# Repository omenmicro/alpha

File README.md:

# OMEN Alpha - [[česky](README-CZ.md)]

_8bit computer, based on 8085 CPU._

- [Essential ICs on AliExpress](https://alitronik.com/omen-alpha-pack/)
- [Essential ICs on eBay](https://alitronik.com/omen-alpha-pack-ebay/)

[BOM - Needed parts](./BOM.md)

I write a book about old computers. Oh, sorry: I mean "vintage computers" from the 80's. My primary goal is to show how one can build an 8bit computer from scratch.

It means: how to set up a CPU, how to connect memories, how to connect peripheral chips, and why to connect...

This computer is a "demo construction": A computer, based on 8085 CPU, with 32 kB of (EEP)ROM and 32 kB of RAM, serial connection and parallel ports. All should be as simple as possible. And here is a result.

ROM
---

Use the last Monitor file - see [sw/Monitor/v4](sw/Monitor/v4)

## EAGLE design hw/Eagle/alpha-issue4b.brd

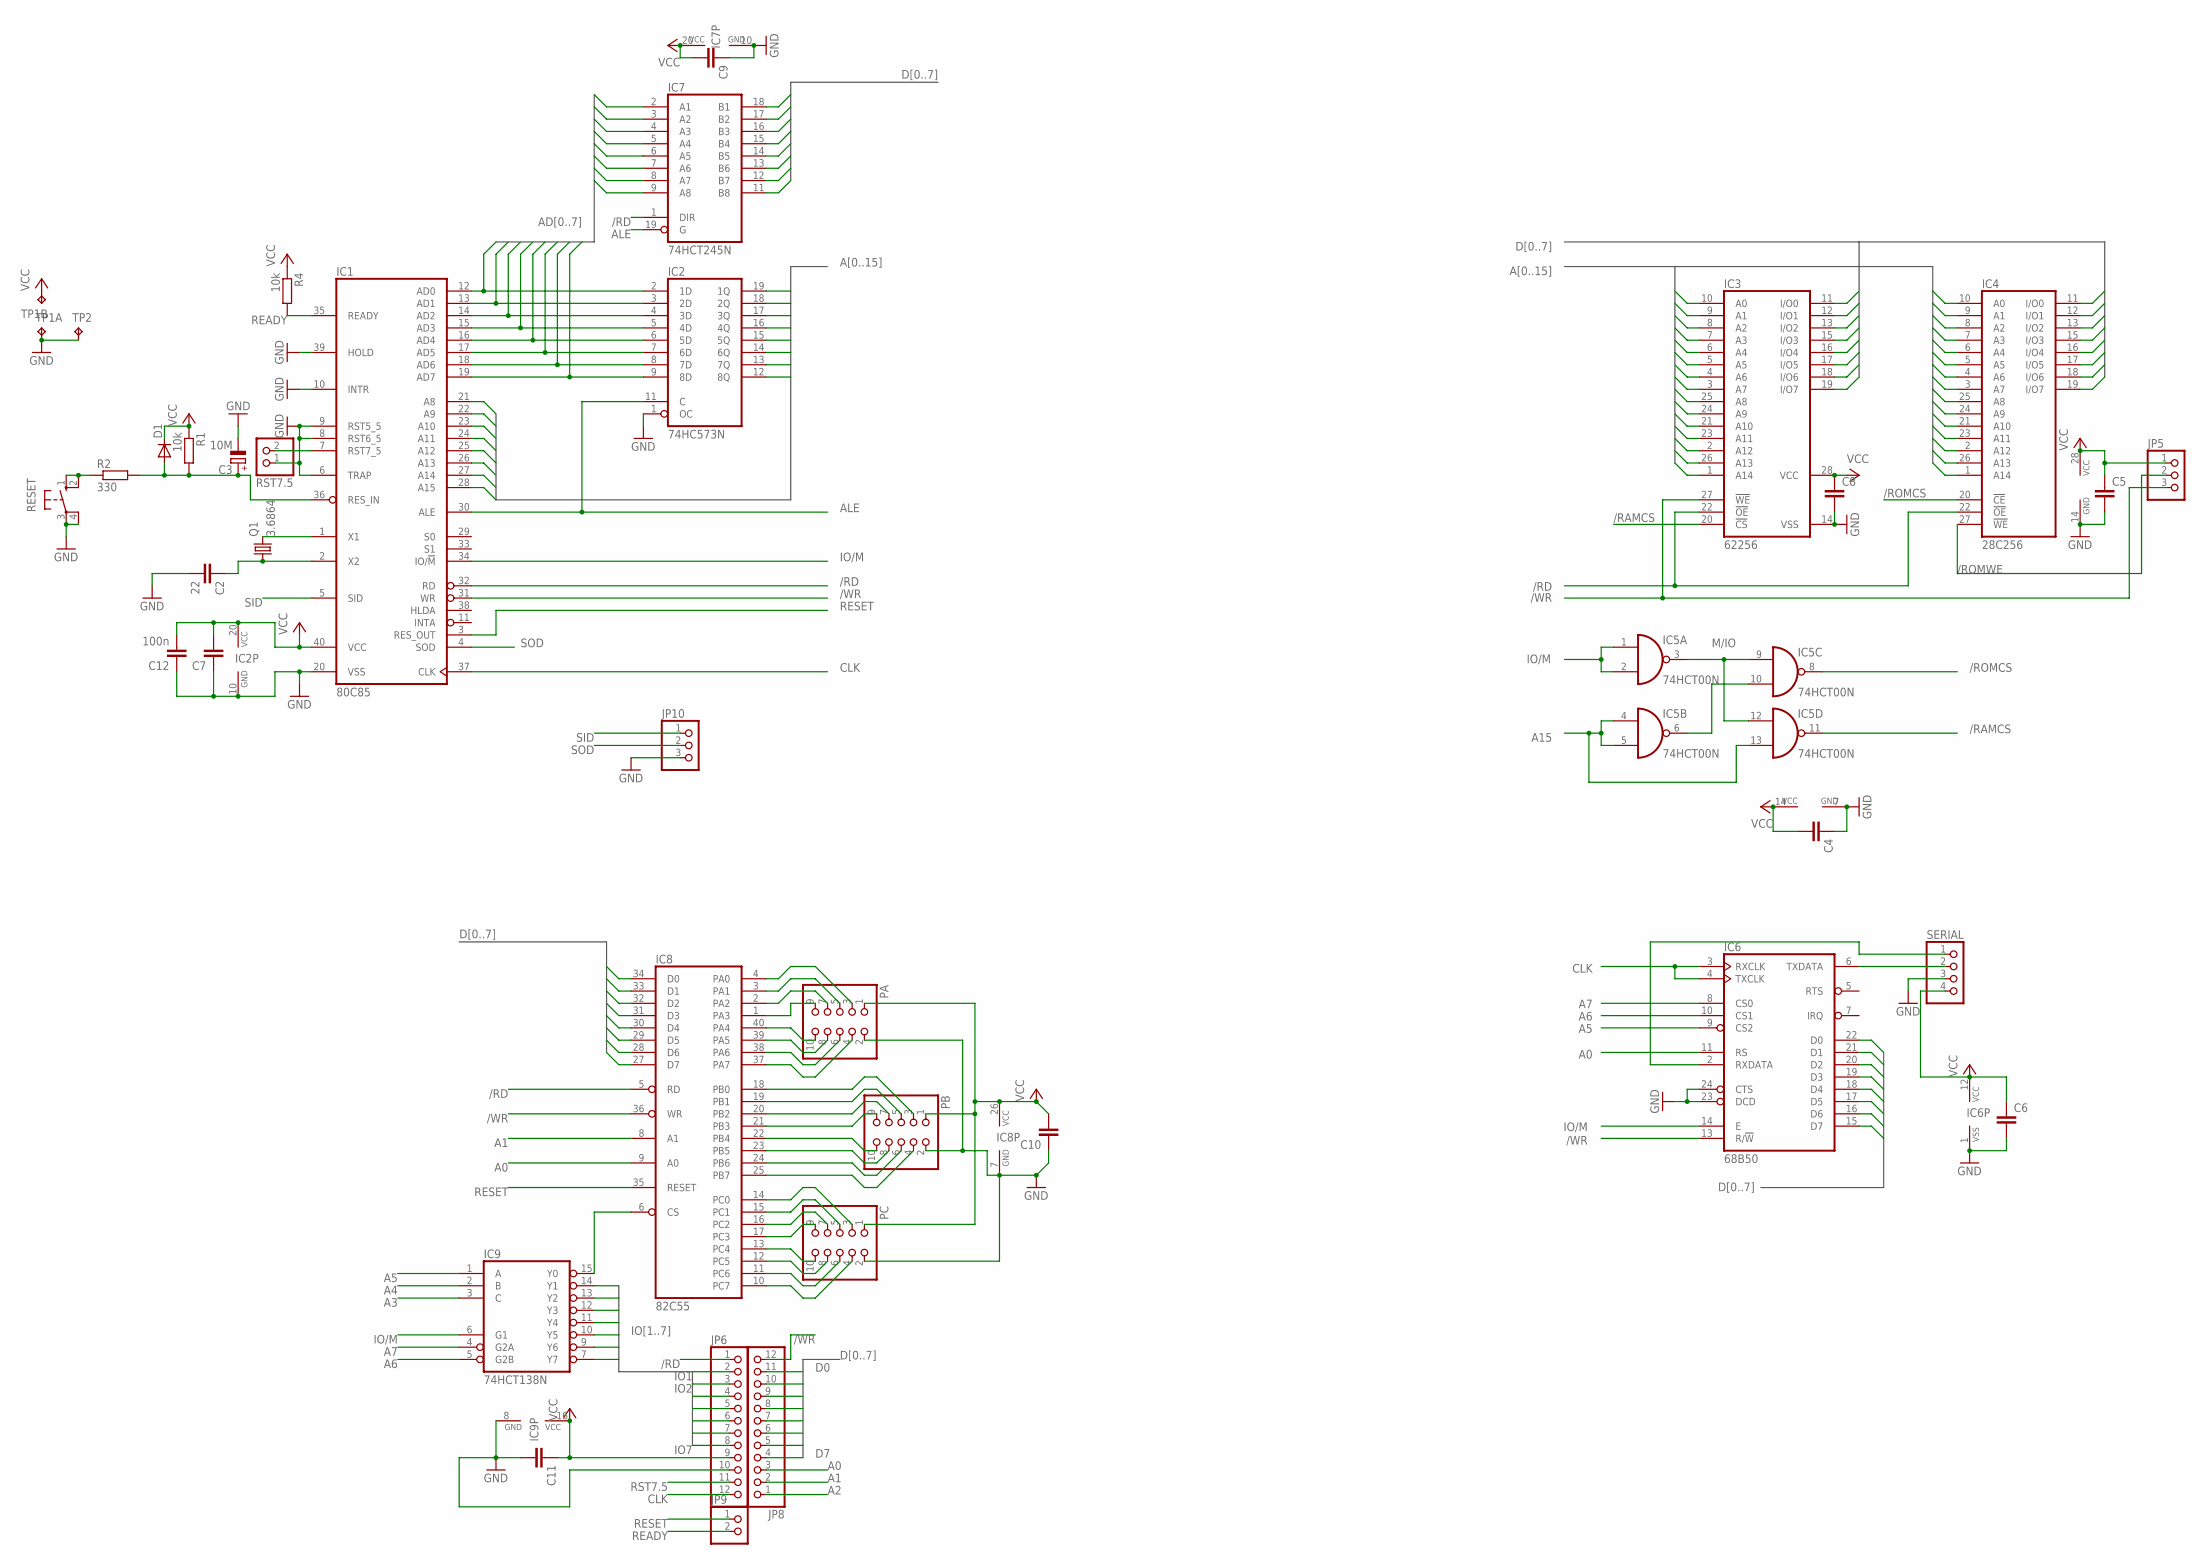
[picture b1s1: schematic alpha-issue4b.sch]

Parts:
C2: 22; C025-040X050
C3: 10M; E5-8,5
C4, C5, C6, C7, C8, C9, C10, C11: C-EU050-025X075; C050-025X075
C12: 100n; C050-025X075
D1: 1N4004; DO41-10
IC1: 80C85; DIL40
IC2: 74HC573N; DIL20
IC3: 62256; DIL28-6
IC4: 28C256; DIL28
IC5: 74HCT00N; DIL14
IC6: 68B50; DIL24
IC7: 74HCT245N; DIL20
IC8: 82C55; DIL40
IC9: 74HCT138N; DIL16
JP5, JP10: PINHD-1X3; 1X03
JP6, JP8: PINHD-1X12; 1X12
JP9: PINHD-1X2; 1X02
PA: PINHD-2X5; 2X05
PB: PINHD-2X5; 2X05
PC: PINHD-2X5; 2X05
Q1: 3.6864; HC49/S
R1: 10k; 0207/10
R2: 330; 0207/10
R4: 10k; 0204/7
RESET: 40-XX; B3F-40XX
RST7.5: PINHD-1X2; 1X02
SERIAL: PINHD-1X4; 1X04
TP1: TP2P2-38-17; P2-38-17
TP2: TPPAD1-17Y; P1-17Y

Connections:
/RAMCS: IC3.20 (!CS), IC5.11 (O)
/RD: IC1.32 (RD), IC3.22 (!OE), IC4.22 (!OE), IC7.1 (DIR), IC8.5 (RD), JP6.1
/ROMCS: IC4.20 (!CE), IC5.8 (O)
/ROMWE: IC4.27 (!WE), JP5.2
/WR: IC1.31 (WR), IC3.27 (!WE), IC6.13 (R/!W), IC8.36 (WR), JP5.3, JP8.12
A0: IC2.19 (1Q), IC3.10 (A0), IC4.10 (A0), IC6.11 (RS), IC8.9 (A0), JP8.3
A1: IC2.18 (2Q), IC3.9 (A1), IC4.9 (A1), IC8.8 (A1), JP8.2
A2: IC2.17 (3Q), IC3.8 (A2), IC4.8 (A2), JP8.1
A3: IC2.16 (4Q), IC3.7 (A3), IC4.7 (A3), IC9.3 (C)
A4: IC2.15 (5Q), IC3.6 (A4), IC4.6 (A4), IC9.2 (B)
A5: IC2.14 (6Q), IC3.5 (A5), IC4.5 (A5), IC6.9 (CS2), IC9.1 (A)
A6: IC2.13 (7Q), IC3.4 (A6), IC4.4 (A6), IC6.10 (CS1), IC9.5 (G2B)
A7: IC2.12 (8Q), IC3.3 (A7), IC4.3 (A7), IC6.8 (CS0), IC9.4 (G2A)
A8: IC1.21 (A8), IC3.25 (A8), IC4.25 (A8)
A9: IC1.22 (A9), IC3.24 (A9), IC4.24 (A9)
A10: IC1.23 (A10), IC3.21 (A10), IC4.21 (A10)
A11: IC1.24 (A11), IC3.23 (A11), IC4.23 (A11)
A12: IC1.25 (A12), IC3.2 (A12), IC4.2 (A12)
A13: IC1.26 (A13), IC3.26 (A13), IC4.26 (A13)
A14: IC1.27 (A14), IC3.1 (A14), IC4.1 (A14)
A15: IC1.28 (A15), IC5.4 (I0), IC5.5 (I1), IC5.13 (I1)
ALE: IC1.30 (ALE), IC2.11 (C), IC7.19 (G)
CLK: IC1.37 (CLK), IC6.3 (RXCLK), IC6.4 (TXCLK), JP6.12
D0: IC3.11 (I/O0), IC4.11 (I/O0), IC6.22 (D0), IC7.18 (B1), IC8.34 (D0), JP8.11
D1: IC3.12 (I/O1), IC4.12 (I/O1), IC6.21 (D1), IC7.17 (B2), IC8.33 (D1), JP8.10
D2: IC3.13 (I/O2), IC4.13 (I/O2), IC6.20 (D2), IC7.16 (B3), IC8.32 (D2), JP8.9
D3: IC3.15 (I/O3), IC4.15 (I/O3), IC6.19 (D3), IC7.15 (B4), IC8.31 (D3), JP8.8
D4: IC3.16 (I/O4), IC4.16 (I/O4), IC6.18 (D4), IC7.14 (B5), IC8.30 (D4), JP8.7
D5: IC3.17 (I/O5), IC4.17 (I/O5), IC6.17 (D5), IC7.13 (B6), IC8.29 (D5), JP8.6
D6: IC3.18 (I/O6), IC4.18 (I/O6), IC6.16 (D6), IC7.12 (B7), IC8.28 (D6), JP8.5
D7: IC3.19 (I/O7), IC4.19 (I/O7), IC6.15 (D7), IC7.11 (B8), IC8.27 (D7), JP8.4
DX0: IC1.12 (AD0), IC2.2 (1D), IC7.2 (A1)
DX1: IC1.13 (AD1), IC2.3 (2D), IC7.3 (A2)
DX2: IC1.14 (AD2), IC2.4 (3D), IC7.4 (A3)
DX3: IC1.15 (AD3), IC2.5 (4D), IC7.5 (A4)
DX4: IC1.16 (AD4), IC2.6 (5D), IC7.6 (A5)
DX5: IC1.17 (AD5), IC2.7 (6D), IC7.7 (A6)
DX6: IC1.18 (AD6), IC2.8 (7D), IC7.8 (A7)
DX7: IC1.19 (AD7), IC2.9 (8D), IC7.9 (A8)
GND: C2.2, C3.-, C4.1, C5.2, C6.2, C7.1, C8.2, C9.1, C10.1, C11.2, C12.1, IC1.6 (TRAP), IC1.8 (RST6_5), IC1.9 (RST5_5), IC1.10 (INTR), IC1.20 (VSS), IC1.39 (HOLD), IC2.1 (OC), IC2.10 (GND), IC3.14 (VSS), IC4.14 (GND), IC5.7 (GND), IC6.1 (VSS), IC6.23 (DCD), IC6.24 (CTS), IC7.10 (GND), IC8.7 (GND), IC9.8 (GND), JP6.10, JP10.3, PA.2, PB.2, PC.2, RESET.3, RESET.4 (P1), RST7.5.1, SERIAL.3, TP1.TP-1, TP2.TP
IO1: IC9.14 (Y1), JP6.2
IO2: IC9.13 (Y2), JP6.3
IO3: IC9.12 (Y3), JP6.4
IO4: IC9.11 (Y4), JP6.5
IO5: IC9.10 (Y5), JP6.6
IO6: IC9.9 (Y6), JP6.7
IO7: IC9.7 (Y7), JP6.8
IO/M: IC1.34 (IO/!M), IC5.1 (I0), IC5.2 (I1), IC6.14 (E), IC9.6 (G1)
M/IO: IC5.3 (O), IC5.9 (I0), IC5.12 (I0)
unnamed: IC1.1 (X1), Q1.2
unnamed: C2.1, IC1.2 (X2), Q1.1
unnamed: IC6.6 (TXDATA), SERIAL.2
unnamed: C3.+, D1.A, IC1.36 (RES_IN), R1.2, R2.2
unnamed: R2.1, RESET.1 (S), RESET.2 (S1)
unnamed: IC5.6 (O), IC5.10 (I1)
unnamed: IC8.1 (PA3), PA.9
unnamed: IC6.2 (RXDATA), SERIAL.1
unnamed: IC8.2 (PA2), PA.7
unnamed: IC8.3 (PA1), PA.5
unnamed: IC8.4 (PA0), PA.3
unnamed: IC8.40 (PA4), PA.10
unnamed: IC8.39 (PA5), PA.8
unnamed: IC8.38 (PA6), PA.6
unnamed: IC8.37 (PA7), PA.4
unnamed: IC8.21 (PB3), PB.9
unnamed: IC8.20 (PB2), PB.7
unnamed: IC8.19 (PB1), PB.5
unnamed: IC8.18 (PB0), PB.3
unnamed: IC8.22 (PB4), PB.10
unnamed: IC8.23 (PB5), PB.8
unnamed: IC8.24 (PB6), PB.6
unnamed: IC8.25 (PB7), PB.4
unnamed: IC8.17 (PC3), PC.9
unnamed: IC8.13 (PC4), PC.10
unnamed: IC8.16 (PC2), PC.7
unnamed: IC8.15 (PC1), PC.5
unnamed: IC8.12 (PC5), PC.8
unnamed: IC8.11 (PC6), PC.6
unnamed: IC8.6 (CS), IC9.15 (Y0)
PORTC0: IC8.14 (PC0), PC.3
PORTC7: IC8.10 (PC7), PC.4
READY: IC1.35 (READY), JP9.2, R4.2
RESET: IC1.3 (RES_OUT), IC8.35 (RESET), JP9.1
RST7.5: IC1.7 (RST7_5), JP6.11, RST7.5.2
SID: IC1.5 (SID), JP10.1
SOD: IC1.4 (SOD), JP10.2
VCC: C4.2, C5.1, C6.1, C7.2, C8.1, C9.2, C10.2, C11.1, C12.2, D1.C, IC1.40 (VCC), IC2.20 (VCC), IC3.28 (VCC), IC4.28 (VCC), IC5.14 (VCC), IC6.12 (VCC), IC7.20 (VCC), IC8.26 (VCC), IC9.16 (VCC), JP5.1, JP6.9, PA.1, PB.1, PC.1, R1.1, R4.1, SERIAL.4, TP1.TP-2

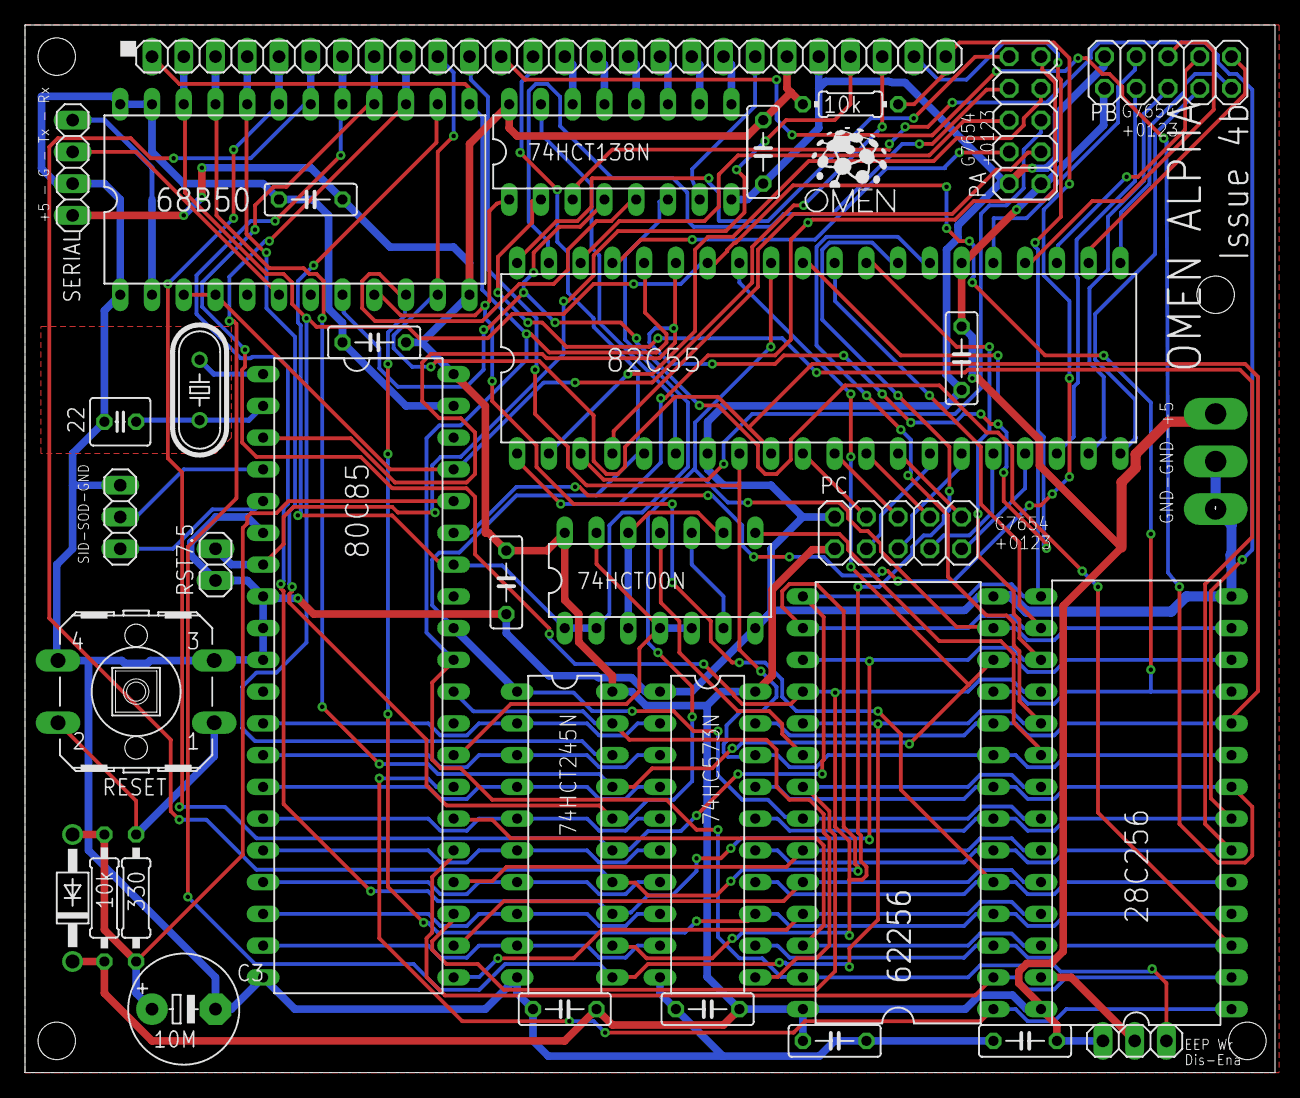
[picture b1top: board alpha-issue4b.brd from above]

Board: 2 copper layers, 100.0 x 83.8 mm, 38 parts (0 on the bottom side), 87 nets.

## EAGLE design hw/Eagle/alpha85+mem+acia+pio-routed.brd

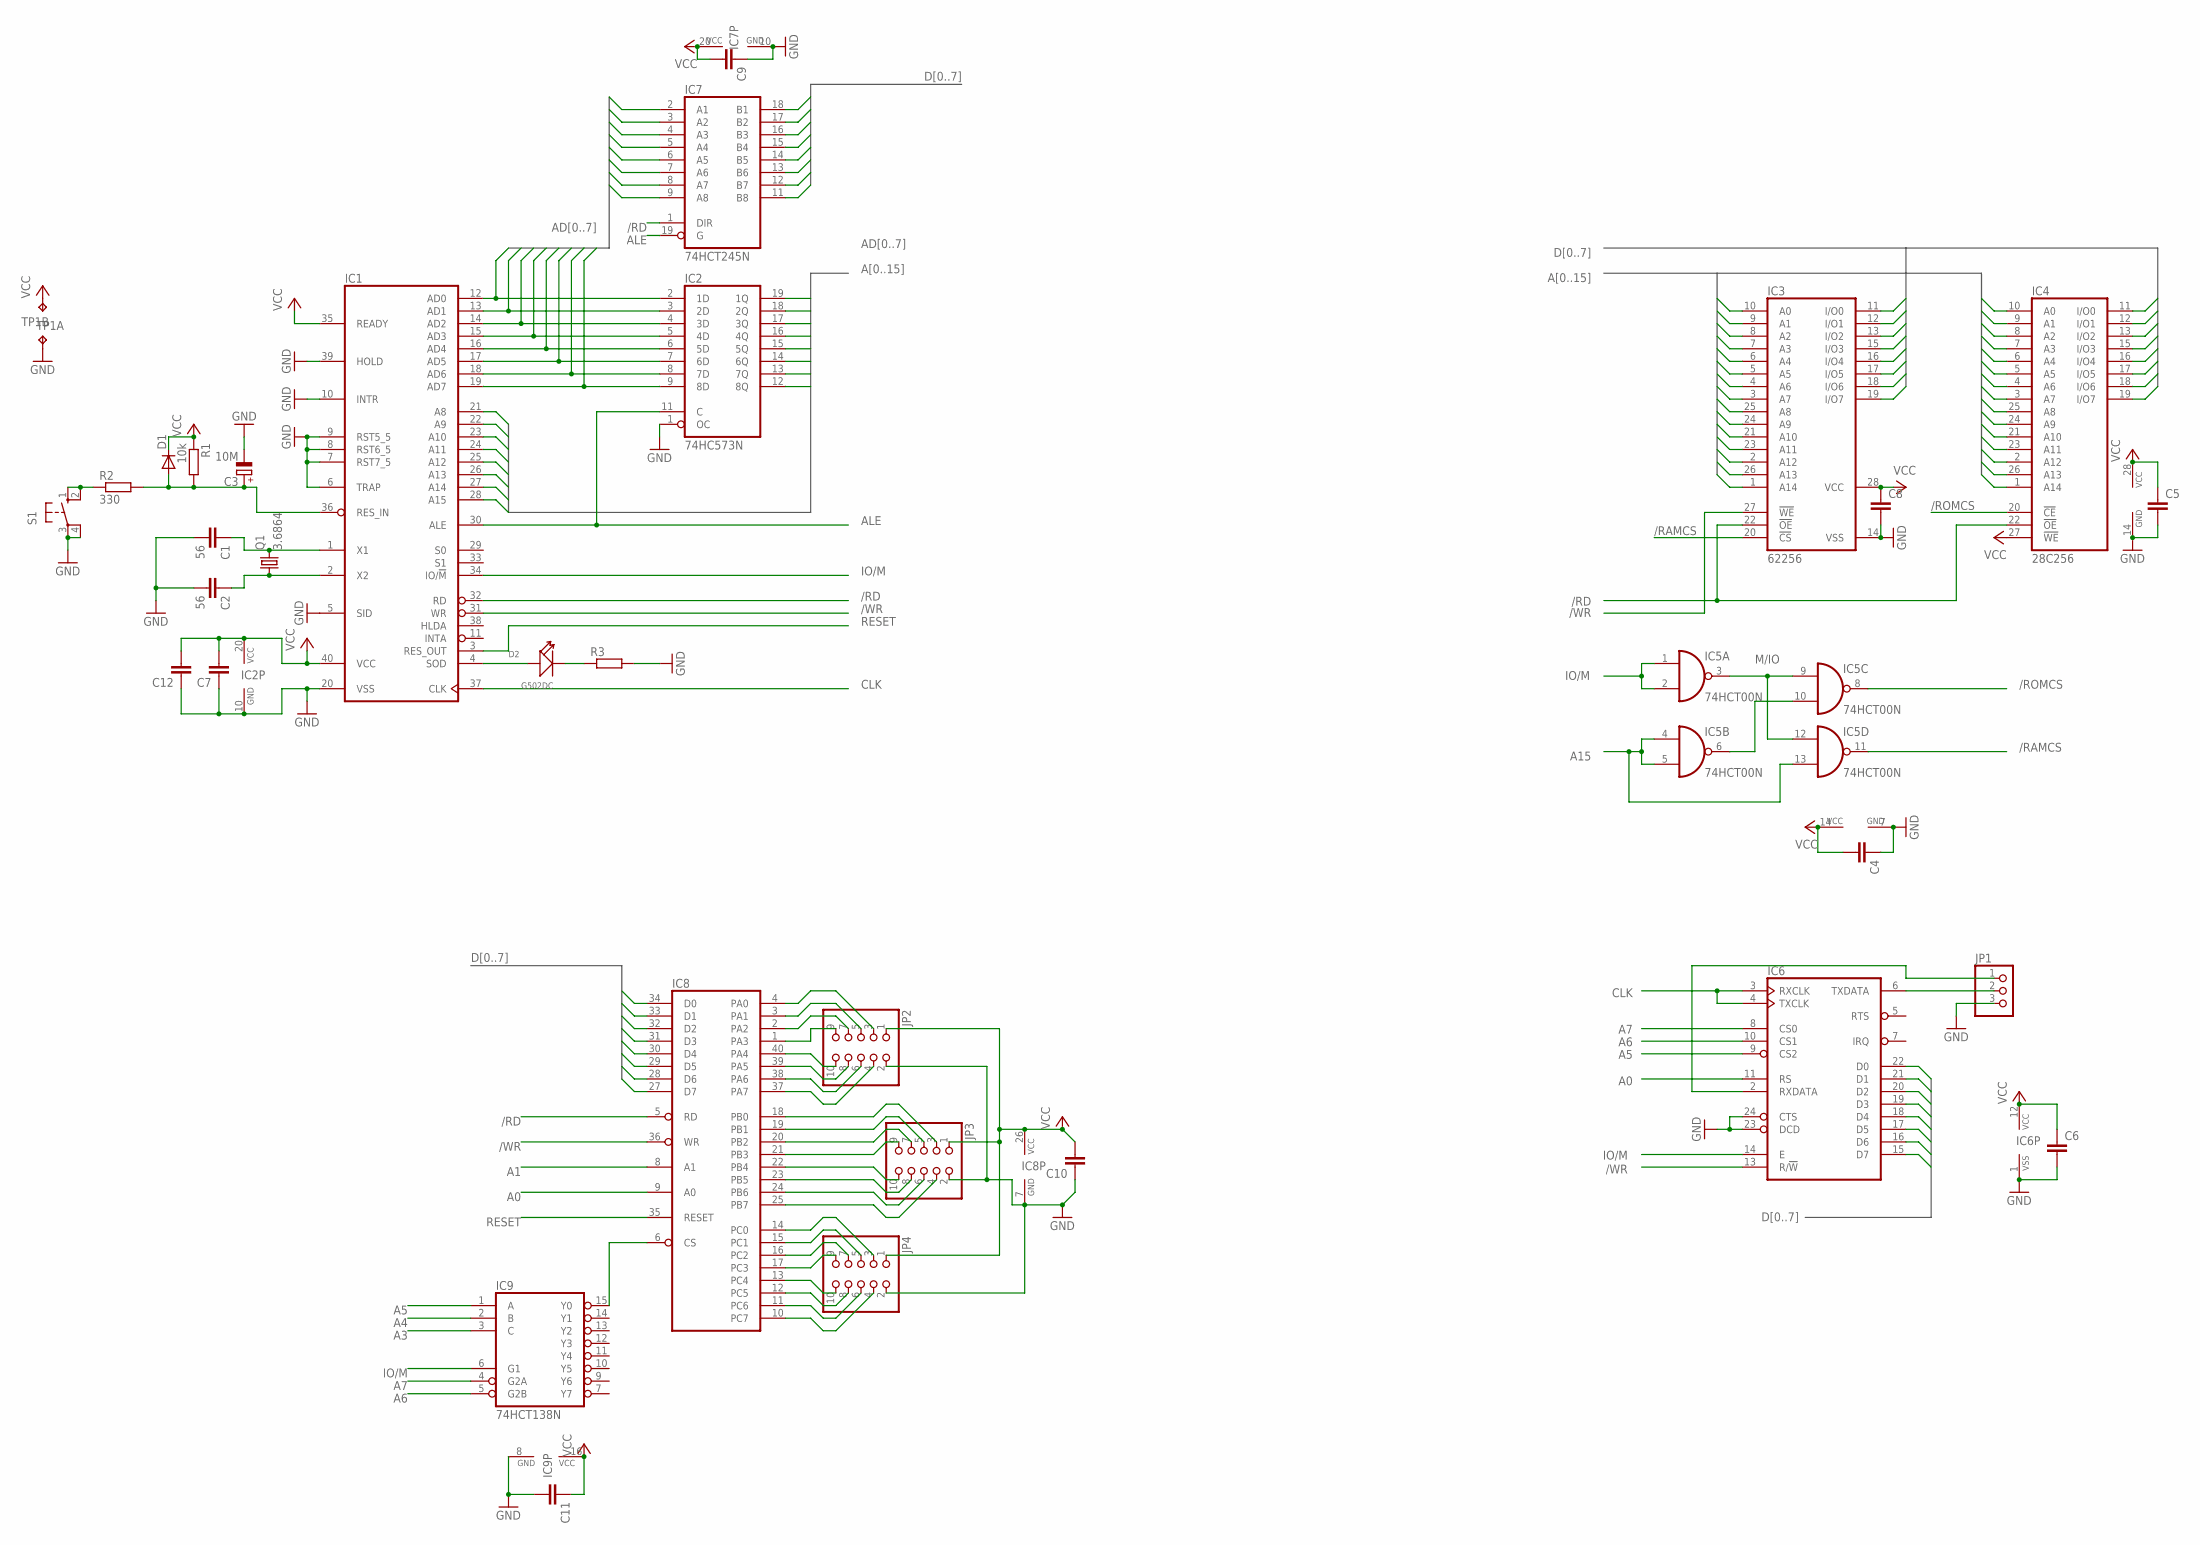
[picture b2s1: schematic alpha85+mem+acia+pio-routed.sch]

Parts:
C1, C2: 56; C025-040X050
C3: 10M; E5-8,5
C4, C5, C6, C7, C8, C9, C10, C11, C12: C-EU050-025X075; C050-025X075
D1: 1N4004; DO41-10
D2: G502DC; LED2-2.54-D5.0MM
IC1: 8085; DIL40
IC2: 74HC573N; DIL20
IC3: 62256; DIL28-6
IC4: 28C256; DIL28
IC5: 74HCT00N; DIL14
IC6: 6850; DIL24
IC7: 74HCT245N; DIL20
IC8: 8255A; DIL40
IC9: 74HCT138N; DIL16
JP1: PINHD-1X3; 1X03
JP2, JP3, JP4: PINHD-2X5; 2X05
Q1: 3.6864; HC49/S
R1: 10k; 0207/10
R2: 330; 0207/10
R3: R-EU_0207/7; 0207/7
S1: 40-XX; B3F-40XX
TP1: TP2P2-38-17; P2-38-17

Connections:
/RAMCS: IC3.20 (!CS), IC5.11 (O)
/RD: IC1.32 (RD), IC3.22 (!OE), IC4.22 (!OE), IC7.1 (DIR), IC8.5 (RD)
/ROMCS: IC4.20 (!CE), IC5.8 (O)
/WR: IC1.31 (WR), IC3.27 (!WE), IC6.13 (R/!W), IC8.36 (WR)
A0: IC2.19 (1Q), IC3.10 (A0), IC4.10 (A0), IC6.11 (RS), IC8.9 (A0)
A1: IC2.18 (2Q), IC3.9 (A1), IC4.9 (A1), IC8.8 (A1)
A2: IC2.17 (3Q), IC3.8 (A2), IC4.8 (A2)
A3: IC2.16 (4Q), IC3.7 (A3), IC4.7 (A3), IC9.3 (C)
A4: IC2.15 (5Q), IC3.6 (A4), IC4.6 (A4), IC9.2 (B)
A5: IC2.14 (6Q), IC3.5 (A5), IC4.5 (A5), IC6.9 (CS2), IC9.1 (A)
A6: IC2.13 (7Q), IC3.4 (A6), IC4.4 (A6), IC6.10 (CS1), IC9.5 (G2B)
A7: IC2.12 (8Q), IC3.3 (A7), IC4.3 (A7), IC6.8 (CS0), IC9.4 (G2A)
A8: IC1.21 (A8), IC3.25 (A8), IC4.25 (A8)
A9: IC1.22 (A9), IC3.24 (A9), IC4.24 (A9)
A10: IC1.23 (A10), IC3.21 (A10), IC4.21 (A10)
A11: IC1.24 (A11), IC3.23 (A11), IC4.23 (A11)
A12: IC1.25 (A12), IC3.2 (A12), IC4.2 (A12)
A13: IC1.26 (A13), IC3.26 (A13), IC4.26 (A13)
A14: IC1.27 (A14), IC3.1 (A14), IC4.1 (A14)
A15: IC1.28 (A15), IC5.4 (I0), IC5.5 (I1), IC5.13 (I1)
ALE: IC1.30 (ALE), IC2.11 (C), IC7.19 (G)
CLK: IC1.37 (CLK), IC6.3 (RXCLK), IC6.4 (TXCLK)
D0: IC3.11 (I/O0), IC4.11 (I/O0), IC6.22 (D0), IC7.18 (B1), IC8.34 (D0)
D1: IC3.12 (I/O1), IC4.12 (I/O1), IC6.21 (D1), IC7.17 (B2), IC8.33 (D1)
D2: IC3.13 (I/O2), IC4.13 (I/O2), IC6.20 (D2), IC7.16 (B3), IC8.32 (D2)
D3: IC3.15 (I/O3), IC4.15 (I/O3), IC6.19 (D3), IC7.15 (B4), IC8.31 (D3)
D4: IC3.16 (I/O4), IC4.16 (I/O4), IC6.18 (D4), IC7.14 (B5), IC8.30 (D4)
D5: IC3.17 (I/O5), IC4.17 (I/O5), IC6.17 (D5), IC7.13 (B6), IC8.29 (D5)
D6: IC3.18 (I/O6), IC4.18 (I/O6), IC6.16 (D6), IC7.12 (B7), IC8.28 (D6)
D7: IC3.19 (I/O7), IC4.19 (I/O7), IC6.15 (D7), IC7.11 (B8), IC8.27 (D7)
DX0: IC1.12 (AD0), IC2.2 (1D), IC7.2 (A1)
DX1: IC1.13 (AD1), IC2.3 (2D), IC7.3 (A2)
DX2: IC1.14 (AD2), IC2.4 (3D), IC7.4 (A3)
DX3: IC1.15 (AD3), IC2.5 (4D), IC7.5 (A4)
DX4: IC1.16 (AD4), IC2.6 (5D), IC7.6 (A5)
DX5: IC1.17 (AD5), IC2.7 (6D), IC7.7 (A6)
DX6: IC1.18 (AD6), IC2.8 (7D), IC7.8 (A7)
DX7: IC1.19 (AD7), IC2.9 (8D), IC7.9 (A8)
GND: C1.2, C2.2, C3.-, C4.1, C5.2, C6.2, C7.1, C8.2, C9.1, C10.1, C11.2, C12.1, IC1.5 (SID), IC1.6 (TRAP), IC1.7 (RST7_5), IC1.8 (RST6_5), IC1.9 (RST5_5), IC1.10 (INTR), IC1.20 (VSS), IC1.39 (HOLD), IC2.1 (OC), IC2.10 (GND), IC3.14 (VSS), IC4.14 (GND), IC5.7 (GND), IC6.1 (VSS), IC6.23 (DCD), IC6.24 (CTS), IC7.10 (GND), IC8.7 (GND), IC9.8 (GND), JP1.3, JP2.2, JP3.2, JP4.2, R3.2, S1.3, S1.4 (P1), TP1.TP-1
IO/M: IC1.34 (IO/!M), IC5.1 (I0), IC5.2 (I1), IC6.14 (E), IC9.6 (G1)
M/IO: IC5.3 (O), IC5.9 (I0), IC5.12 (I0)
unnamed: C1.1, IC1.1 (X1), Q1.2
unnamed: C2.1, IC1.2 (X2), Q1.1
unnamed: D2.+, IC1.4 (SOD)
unnamed: D2.-, R3.1
unnamed: IC6.6 (TXDATA), JP1.2
unnamed: C3.+, D1.A, IC1.36 (RES_IN), R1.2, R2.2
unnamed: R2.1, S1.1 (S), S1.2 (S1)
unnamed: IC5.6 (O), IC5.10 (I1)
unnamed: IC8.1 (PA3), JP2.9
unnamed: IC6.2 (RXDATA), JP1.1
unnamed: IC8.2 (PA2), JP2.7
unnamed: IC8.3 (PA1), JP2.5
unnamed: IC8.4 (PA0), JP2.3
unnamed: IC8.40 (PA4), JP2.10
unnamed: IC8.39 (PA5), JP2.8
unnamed: IC8.38 (PA6), JP2.6
unnamed: IC8.37 (PA7), JP2.4
unnamed: IC8.21 (PB3), JP3.9
unnamed: IC8.20 (PB2), JP3.7
unnamed: IC8.19 (PB1), JP3.5
unnamed: IC8.18 (PB0), JP3.3
unnamed: IC8.22 (PB4), JP3.10
unnamed: IC8.23 (PB5), JP3.8
unnamed: IC8.24 (PB6), JP3.6
unnamed: IC8.25 (PB7), JP3.4
unnamed: IC8.17 (PC3), JP4.9
unnamed: IC8.13 (PC4), JP4.10
unnamed: IC8.16 (PC2), JP4.7
unnamed: IC8.15 (PC1), JP4.5
unnamed: IC8.14 (PC0), JP4.3
unnamed: IC8.12 (PC5), JP4.8
unnamed: IC8.11 (PC6), JP4.6
unnamed: IC8.10 (PC7), JP4.4
unnamed: IC8.6 (CS), IC9.15 (Y0)
RESET: IC1.3 (RES_OUT), IC8.35 (RESET)
VCC: C4.2, C5.1, C6.1, C7.2, C8.1, C9.2, C10.2, C11.1, C12.2, D1.C, IC1.35 (READY), IC1.40 (VCC), IC2.20 (VCC), IC3.28 (VCC), IC4.27 (!WE), IC4.28 (VCC), IC5.14 (VCC), IC6.12 (VCC), IC7.20 (VCC), IC8.26 (VCC), IC9.16 (VCC), JP2.1, JP3.1, JP4.1, R1.1, TP1.TP-2

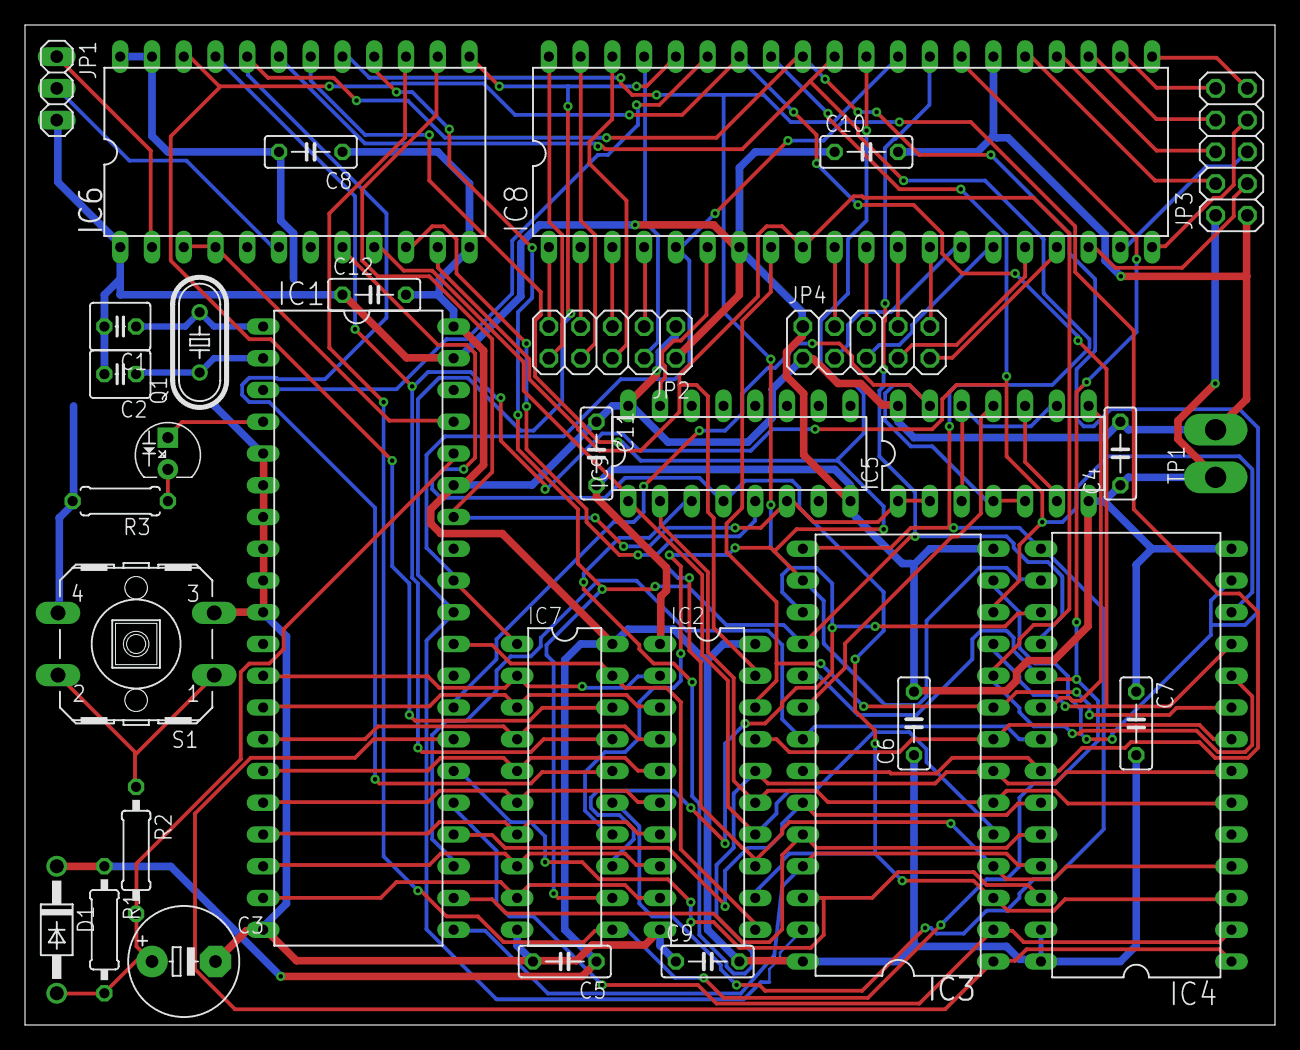
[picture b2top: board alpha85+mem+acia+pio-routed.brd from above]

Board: 2 copper layers, 100.0 x 80.0 mm, 33 parts (0 on the bottom side), 77 nets.

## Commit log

2018-05-06 Init
2018-05-06 Readme
2018-05-06 Partlist
2018-05-07 Datasheets
2018-05-07 Schematic revised
2018-05-07 Alpha.emu for ASM80
2018-05-13 Monitor V3
2018-05-26 Added MON85 by Dave Dunfield / Roman Borik
2018-05-26 MON85: ready-made images for EEPROM
2018-06-17 issue 2 schematics,board
2018-06-17 Gerber
2018-06-17 BRD REV
2018-07-08 TM1638
2018-07-28 Assembly instructions
2018-07-28 Parts and places
2018-08-05 docs
2018-08-12 Issue 4
2018-08-18 Manual
2018-08-19 Manual in Czech
2018-08-28 Badge
2018-09-21 Manual with artwork by Svejda+Goldmann
2018-10-26 New MON85 fix
2018-12-25 8080 exerciser added
2018-12-25 Monitor v3 fixed, HEX checksum computed
2018-12-27 EEPROM writer
2019-03-31 packs
2019-05-12 EN/CZ
2019-05-17 Issue 4a
    Added:
    - holes
    - pin Vcc for serial port
    74138 moved away from 6850
2019-05-19 contributions
2019-05-25 issue 4b - new silk
2019-05-31 EEPROM write with data polling
2019-05-31 Issue 4B
2019-06-15 Monitor v4
2019-06-15 err fix
2019-08-26 Patreon
2020-08-15 Bugfix for eeprom writer, thx to Roman Borik
